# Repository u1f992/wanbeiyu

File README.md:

# Wanbeiyu

🍊 Wanbeiyu (晩白柚) is a project designed to enable control of the Nintendo 3DS series through serial communication. It succeeds the Qingpi project.

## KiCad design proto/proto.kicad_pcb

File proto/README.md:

# ATmega32U4設計メモ

## 電源回路

<figure>
<figcaption><a href="https://ww1.microchip.com/downloads/en/DeviceDoc/Atmel-7766-8-bit-AVR-ATmega16U4-32U4_Datasheet.pdf">Atmel-7766J-USB-ATmega16U4/32U4-Datasheet_04/2016</a> P.258「21.3.2 Self Powered Device」Figure 21-5. Typical Self Powered Application with 3.4V to 5.5V I/O</figcaption>

</figure>

## セラロック選定

ATmega32U4を搭載した小型のArduino互換基板に搭載されているセラロックのベース品番は、村田製作所の「CSTNE16M0V\*」のようだ（[参考](https://electronics.stackexchange.com/a/665240)）。適合するセラロックは「[SimSurfing: IC-タイミングデバイス検索ツール](https://ds.murata.co.jp/simsurfing/ic-timing-device.html)」で検索できる。ATmega32U4そのものは登録されていないので、ATmega32M1、ATmega32C1で検索した。

<details>
<summary>2025-05-09T04:07:26.697Z</summary>
<figure>
<figcaption><a href="https://ds.murata.co.jp/simsurfing/ic-timing-device.html?lcid=ja&icmaker=Microchip&icname=ATmega32M1&tdhin=CSTNE16M0V&spec_application=0&supplystatus=0&kosa=0&tempL=0&tempH=0">ATmega32M1</a></figcaption>

|IC品名|IC備考|ICメーカー|品番|適用用途[^1]|ステータス[^2]|発振周波数\[MHz]|周波数許容偏差|CL1\[pF][^3]|CL2\[pF][^4]|Rf\[ohm]|Rd\[ohm]|IC電圧(min.)\[V]|IC電圧(max.)\[V]|使用温度(min.)\[deg.C]|使用温度(max.)\[deg.C]|IC Application|
|---|---|---|---|:---:|:---:|---|---|---|---|---|---|---|---|---|---|---|
|ATmega32M1|CKSEL:111|Microchip|CSTNE16M0V53C000R0|`APS`|`生産中`|16|+/-0.5%|15|15|Open|0|4.5|5.5|-40|125||
|ATmega32M1|CKSEL:111|Microchip|CSTNE16M0VH3C000R0|`APS`|`生産中`|16|+/-0.07%|15|15|Open|0|4.5|5.5|-40|125||

</figure>

[^1]: <dl><dt><code>CE</code></dt><dd>民生機器</dd><dt><code>IE</code></dt><dd>産業機器</dd><dt><code>AIC</code></dt><dd>自動車用インフォテインメント / コンフォート機器</dd><dt><code>APS</code></dt><dd>自動車用パワートレイン / セーフティ機器</dd><dt><code>MAB</code></dt><dd>医療機器 [GHTF A/B]</dd><dt><code>MC</code></dt><dd>医療機器 [GHTF C]</dd><dt><code>MD</code></dt><dd>医療機器 [GHTF D]</dd><dt><code>MeI</code></dt><dd>インプラント除く医療機器 [GHTF A/B/C]</dd><dt><code>MI</code></dt><dd>インプラント医療機器または医療機器 [GHTF D]</dd><dt><code>MeS</code></dt><dd>インプラント・手術・自動投与用途除く医療機器 [GHTF A/B/C]</dd><dt><code>ME</code></dt><dd>モバイル機器</dd><dt><code>MC</code></dt><dd>モバイル通信</dd><dt><code>IeT</code></dt><dd>運輸・設備・商用エネルギー関連を除く産業機器</dd><dt><code>CDT</code></dt><dd>民生機器-差動伝送</dd><dt><code>HDD</code></dt><dd>HDD</dd><dt><code>DFD</code></dt><dd>重送検知</dd><dt><code>AaM</code></dt><dd>自動車用機器 <a href="https://www.murata.com/contactform?Product=Capacitor">[ムラタへ問合せ要]</a></dd><dt><code>MaM</code></dt><dd>医療機器 <a href="https://www.murata.com/contactform?Product=Capacitor">[ムラタへ問合せ要]</a></dd></dl>
[^2]: <figure><figcaption>「製品ステータス」の説明</figcaption><dl><dt><code>開発中</code></dt><dd>開発中の製品です。サンプル対応可否、量産時期についてはお問い合わせください。</dd><dt><code>生産中</code></dt><dd>量産、販売中の製品です。</dd><dt><code>NRND</code></dt><dd>新モデルへの部品採用を控えていただきたい製品です。<br>(Not Recommended for New Design)</dd><dt><code>生産中止予定</code></dt><dd>生産中止予定の製品であり、最終受注期限及び最終生産時期が表示されている場合があります。<br>最終受注期限までに、必要数量の連絡をお願いします。</dd><dt><code>生産中止</code></dt><dd>生産を中止しており、ご注文を受け付けていない製品です。</dd></dl></figure>
[^3]: 水晶振動子：外付け容量<br>セラロック：内蔵容量
[^4]: 水晶振動子：外付け容量<br>セラロック：内蔵容量

<figure>
<figcaption><a href="https://ds.murata.co.jp/simsurfing/ic-timing-device.html?lcid=ja&icmaker=Microchip&icname=ATmega32C1&tdhin=CSTNE16M0V&spec_application=0&supplystatus=0&kosa=0&tempL=0&tempH=0">ATmega32C1</a></figcaption>

|IC品名|IC備考|ICメーカー|品番|適用用途[^1]|ステータス[^2]|発振周波数\[MHz]|周波数許容偏差|CL1\[pF][^3]|CL2\[pF][^4]|Rf\[ohm]|Rd\[ohm]|IC電圧(min.)\[V]|IC電圧(max.)\[V]|使用温度(min.)\[deg.C]|使用温度(max.)\[deg.C]|IC Application|
|---|---|---|---|:---:|:---:|---|---|---|---|---|---|---|---|---|---|---|
|ATmega32C1|CKSEL:111|Microchip|CSTNE16M0V53C000R0|`APS`|`生産中`|16|+/-0.5%|15|15|Open|0|4.5|5.5|-40|125||
|ATmega32C1|CKSEL:111|Microchip|CSTNE16M0VH3C000R0|`APS`|`生産中`|16|+/-0.07%|15|15|Open|0|4.5|5.5|-40|125||

</figure>
</details>

[CSTNE16M0V53C000R0](https://www.digikey.jp/ja/products/detail/murata-electronics/CSTNE16M0V53C000R0/8747730)と[CSTNE16M0VH3C000R0](https://www.digikey.jp/ja/products/detail/murata-electronics/CSTNE16M0VH3C000R0/8747732)の違いは周波数許容偏差で、後者のほうが高精度になっている。前者のほうが安価なので、こちらを使用する。

- [CSTNE16M0V53C000R0|セラミック発振子/水晶振動子|タイミングデバイス|村田製作所](https://www.murata.com/ja-jp/products/productdetail?partno=CSTNE16M0V53C000R0)
- [CSTNE16M0V53C000R0 footprint & symbol by Murata | SnapMagic Search](https://www.snapeda.com/parts/CSTNE16M0V53C000R0/Murata/view-part/)

## その他

### DS4424（DS4424N+／DS4424N+T&R）

> T&R = Tape and reel.
> 
> [DS4422-DS4424.pdf](https://www.analog.com/media/en/technical-documentation/data-sheets/DS4422-DS4424.pdf), 19-4744; Rev 2; 9/17, p.1

- [DS4424 Datasheet and Product Info | Analog Devices](https://www.analog.com/en/products/ds4424.html)
- ★[DS4424N+ footprint, schematic symbol and 3D model by Analog Devices](https://componentsearchengine.com/part-view/DS4424N%2B/Analog%20Devices)（SamacSys）
- [DS4424N+T&R footprint, schematic symbol and 3D model by Analog Devices](https://componentsearchengine.com/part-view/DS4424N%2BT%26R/Analog%20Devices)（SamacSys）
- [Analog Devices / Maxim Integrated ds4424n+: Symbol, Footprint, 3D STEP Model | Ultra Librarian](https://app.ultralibrarian.com/details/bd464822-1067-11e9-ab3a-0a3560a4cccc/Analog-Devices-Maxim-Integrated/ds4424n-?uid=124205470)
- [Analog Devices / Maxim Integrated DS4424N+T&R: Symbol, Footprint, 3D STEP Model | Ultra Librarian](https://app.ultralibrarian.com/details/f838bba7-106d-11e9-ab3a-0a3560a4cccc/Analog-Devices-Maxim-Integrated/DS4424N-T-R?uid=124205471)
- [DS4424N+ footprint & symbol by Analog Devices | SnapMagic Search](https://www.snapeda.com/parts/DS4424N+/Analog%20Devices/view-part/)
- [DS4424N+T&R footprint & symbol by Analog Devices | SnapMagic Search](https://www.snapeda.com/parts/DS4424N%2BT%26R/Analog%20Devices/view-part/)

SamacSysには「This model has been built in collaboration with the manufacturer.」とある。品番がシンプルな方がファイルの取り回しにトラブルがないのでDS4424N+を使用。

### MCP659（MCP659-E/ML）

- [MCP659 | Microchip Technology](https://www.microchip.com/en-us/product/mcp659)
- [MCP659-E/ML footprint, schematic symbol and 3D model by Microchip](https://componentsearchengine.com/part-view/MCP659-E%2FML/Microchip)（SamacSys）
- [Microchip MCP659-E/ML: Symbol, Footprint, 3D STEP Model | Ultra Librarian](https://app.ultralibrarian.com/details/e2c9e99d-c6b2-11e9-ab3a-0a3560a4cccc/Microchip/MCP659-E-ML?uid=20012028)
- [MCP659-E/ML footprint & symbol by Microchip | SnapMagic Search](https://www.snapeda.com/parts/MCP659-E/ML/Microchip/view-part/)

### AD8403（AD8403ARU1／AD8403ARUZ1）

> Z = RoHS Compliant Part.
> 
> [AD8400_8402_8403.pdf](https://www.analog.com/media/en/technical-documentation/data-sheets/AD8400_8402_8403.pdf), Rev. E, p.31

- [AD8403 Datasheet and Product Info | Analog Devices](https://www.analog.com/en/products/ad8403.html)
- [AD8403ARUZ1-REEL footprint, schematic symbol and 3D model by Analog Devices](https://componentsearchengine.com/part-view/AD8403ARUZ1-REEL/Analog%20Devices)（SamacSys）
- [Analog Devices Inc AD8403ARUZ1: Symbol, Footprint, 3D STEP Model | Ultra Librarian](https://app.ultralibrarian.com/details/6c0e6e13-106d-11e9-ab3a-0a3560a4cccc/Analog-Devices-Inc/AD8403ARUZ1?uid=446994)
- [Analog Devices Inc AD8403ARUZ1-REEL: Symbol, Footprint, 3D STEP Model | Ultra Librarian](https://app.ultralibrarian.com/details/6c0e708d-106d-11e9-ab3a-0a3560a4cccc/Analog-Devices-Inc/AD8403ARUZ1-REEL?uid=446995)

### MAX14662（MAX14662ETI+／MAX14662ETI+T）

> T = Tape and reel
> 
> [MAX14662.pdf](https://www.analog.com/media/en/technical-documentation/data-sheets/MAX14662.pdf), 19-7308; Rev 1; 6/14, p.22

- [MAX14662 Datasheet and Product Info | Analog Devices](https://www.analog.com/en/products/max14662.html)
- [MAX14662ETI+ footprint, schematic symbol and 3D model by Analog Devices](https://componentsearchengine.com/part-view/MAX14662ETI%2B/Analog%20Devices)（SamacSys）
- [MAX14662ETI+T footprint, schematic symbol and 3D model by Analog Devices](https://componentsearchengine.com/part-view/MAX14662ETI%2BT/Analog%20Devices)（SamacSys）
- [Analog Devices / Maxim Integrated MAX14662ETI+: Symbol, Footprint, 3D STEP Model | Ultra Librarian](https://app.ultralibrarian.com/details/9a478c29-10a1-11e9-ab3a-0a3560a4cccc/Analog-Devices-Maxim-Integrated/MAX14662ETI-?uid=124207957)
- [Analog Devices / Maxim Integrated MAX14662ETI+T: Symbol, Footprint, 3D STEP Model | Ultra Librarian](https://app.ultralibrarian.com/details/98663d0d-10a3-11e9-ab3a-0a3560a4cccc/Analog-Devices-Maxim-Integrated/MAX14662ETI-T?uid=124207958)
- [MAX14662ETI+ footprint & symbol by Analog Devices | SnapMagic Search](https://www.snapeda.com/parts/MAX14662ETI%2B/Analog%20Devices/view-part/)
- [MAX14662ETI+T footprint & symbol by Analog Devices | SnapMagic Search](https://www.snapeda.com/parts/MAX14662ETI%2BT/Analog%20Devices/view-part/)
- [MAX14662ETI+ footprint & symbol by Maxim Integrated | SnapMagic Search](https://www.snapeda.com/parts/MAX14662ETI%2B/Maxim%20Integrated%20Products/view-part/)
- [MAX14662ETI+T footprint & symbol by Maxim Integrated | SnapMagic Search](https://www.snapeda.com/parts/MAX14662ETI%2BT/Maxim%20Integrated%20Products/view-part/)

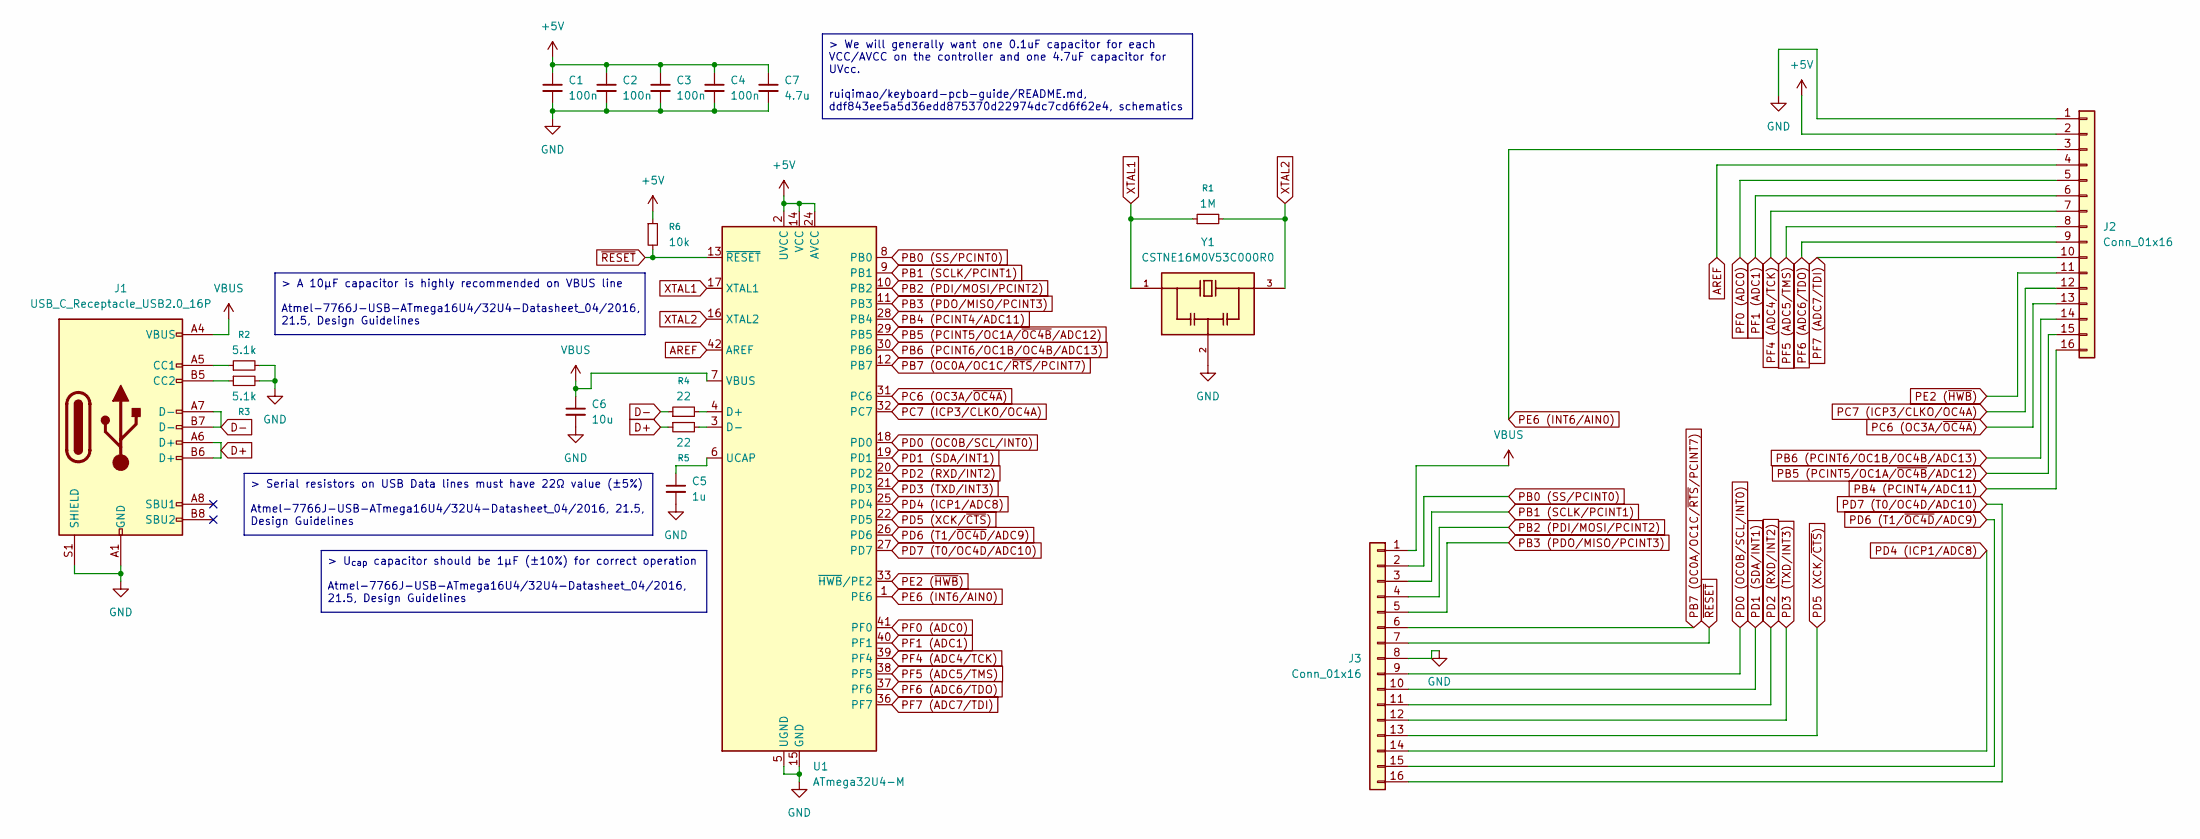
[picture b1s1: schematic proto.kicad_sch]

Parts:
C1, C2, C3, C4: 100n; C_0402_1005Metric
C5: 1u; C_0402_1005Metric
C6: 10u; C_0402_1005Metric
C7: 4.7u; C_0402_1005Metric
J1: USB_C_Receptacle_USB2.0_16P; USB_C_Receptacle_HRO_TYPE-C-31-M-12
J2, J3: Conn_01x16; PinHeader_1x16_P2.54mm_Vertical
R1: 1M; R_0402_1005Metric
R2, R3: 5.1k; R_0402_1005Metric
R4, R5: 22; R_0402_1005Metric
R6: 10k; R_0402_1005Metric
U1: ATmega32U4-M; QFN-44-1EP_7x7mm_P0.5mm_EP5.2x5.2mm
Y1: CSTNE16M0V53C000R0; OSC_CSTNE16M0V53C000R0; PARTREV JGC42-8853B

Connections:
+5V: C1.1, C2.1, C3.1, C4.1, C7.1, J2.2, R6.1, U1.2 (UVCC), U1.14 (VCC), U1.24 (AVCC), U1.34 (VCC), U1.44 (AVCC)
AREF: J2.4, U1.42 (AREF)
D+: J1.A6 (D+), J1.B6 (D+), R5.1
D-: J1.A7 (D-), J1.B7 (D-), R4.1
GND: C1.2, C2.2, C3.2, C4.2, C5.2, C6.2, C7.2, J1.A1 (GND), J1.A12 (GND), J1.B1 (GND), J1.B12 (GND), J1.S1 (SHIELD), J2.1, J3.8, R2.2, R3.2, U1.5 (UGND), U1.15 (GND), U1.23 (GND), U1.35 (GND), U1.43 (GND), U1.45 (GND), Y1.2
unnamed: J1.A5 (CC1), R2.1
unnamed: J1.B5 (CC2), R3.1
unnamed: R4.2, U1.4 (D+)
unnamed: R5.2, U1.3 (D-)
unnamed: C5.1, U1.6 (UCAP)
PB0 (SS/PCINT0): J3.2, U1.8 (PB0)
PB1 (SCLK/PCINT1): J3.3, U1.9 (PB1)
PB2 (PDI/MOSI/PCINT2): J3.4, U1.10 (PB2)
PB3 (PDO/MISO/PCINT3): J3.5, U1.11 (PB3)
PB4 (PCINT4/ADC11): J2.16, U1.28 (PB4)
PB5 (PCINT5/OC1A/~OC4B/ADC12): J2.15, U1.29 (PB5)
PB6 (PCINT6/OC1B/OC4B/ADC13): J2.14, U1.30 (PB6)
PB7 (OC0A/OC1C/~RTS/PCINT7): J3.6, U1.12 (PB7)
PC6 (OC3A/~OC4A): J2.13, U1.31 (PC6)
PC7 (ICP3/CLKO/OC4A): J2.12, U1.32 (PC7)
PD0 (OC0B/SCL/INT0): J3.9, U1.18 (PD0)
PD1 (SDA/INT1): J3.10, U1.19 (PD1)
PD2 (RXD/INT2): J3.11, U1.20 (PD2)
PD3 (TXD/INT3): J3.12, U1.21 (PD3)
PD4 (ICP1/ADC8): J3.14, U1.25 (PD4)
PD5 (XCK/~CTS): J3.13, U1.22 (PD5)
PD6 (T1/~OC4D/ADC9): J3.15, U1.26 (PD6)
PD7 (T0/OC4D/ADC10): J3.16, U1.27 (PD7)
PE2 (~HWB): J2.11, U1.33 (~HWB/PE2)
PE6 (INT6/AIN0): J2.3, U1.1 (PE6)
PF0 (ADC0): J2.5, U1.41 (PF0)
PF1 (ADC1): J2.6, U1.40 (PF1)
PF4 (ADC4/TCK): J2.7, U1.39 (PF4)
PF5 (ADC5/TMS): J2.8, U1.38 (PF5)
PF6 (ADC6/TDO): J2.9, U1.37 (PF6)
PF7 (ADC7/TDI): J2.10, U1.36 (PF7)
VBUS: C6.1, J1.A4 (VBUS), J1.A9 (VBUS), J1.B4 (VBUS), J1.B9 (VBUS), J3.1, U1.7 (VBUS)
XTAL1: R1.1, U1.17 (XTAL1), Y1.1
XTAL2: R1.2, U1.16 (XTAL2), Y1.3
~RESET: J3.7, R6.2, U1.13 (~RESET)

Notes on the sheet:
> A 10µF capacitor is highly recommended on VBUS line Atmel-7766J-USB-ATmega16U4/32U4-Datasheet_04/2016, 21.5, Design Guidelines
> U_{cap} capacitor should be 1µF (±10%) for correct operation Atmel-7766J-USB-ATmega16U4/32U4-Datasheet_04/2016, 21.5, Design Guidelines
> Serial resistors on USB Data lines must have 22Ω value (±5%) Atmel-7766J-USB-ATmega16U4/32U4-Datasheet_04/2016, 21.5, Design Guidelines
> We will generally want one 0.1uF capacitor for each VCC/AVCC on the controller and one 4.7uF capacitor for UVcc. ruiqimao/keyboard-pcb-guide/README.md, ddf843ee5a5d36edd875370d22974dc7cd6f62e4, schematics

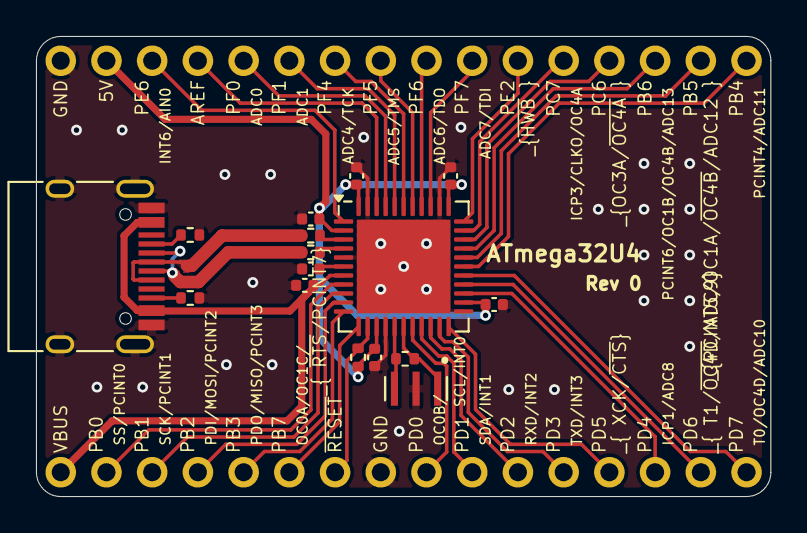
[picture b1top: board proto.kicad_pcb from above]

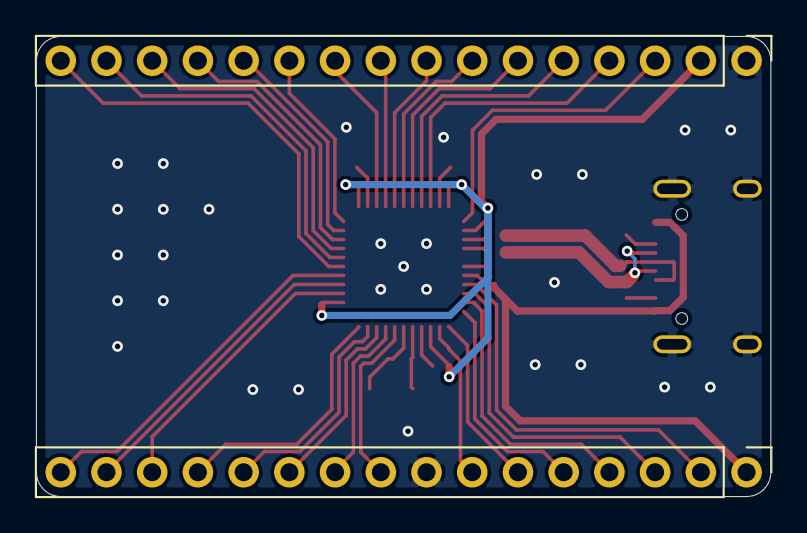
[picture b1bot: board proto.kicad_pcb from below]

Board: 2 copper layers, 40.8 x 25.6 mm, 18 parts (2 on the bottom side), 40 nets.

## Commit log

2025-01-16 Add files
2025-01-16 Create LICENSE
2025-03-16 Update core
2025-03-23 temp
2025-03-26 Use new HAL
2025-03-26 Unify button states into a 16-bit bitfield
2025-03-26 Add test
2025-03-26 Read input from HAL
2025-03-27 Add helper.h
2025-03-27 Inverts pin assignments
2025-03-27 Refactor console_set to use function pointer array
2025-03-27 Replace wanbeiyu_t with static singleton instance
2025-03-27 Extract parser logic into separate module
2025-03-27 Modularize components
2025-03-27 Add license notice
2025-03-27 Add tests (buttons, touch_screen)
2025-03-28 Add documents
2025-03-29 Fix C Stick
2025-03-30 Add hook
2025-03-30 firmware
2025-03-30 Format
2025-03-30 Extend hooks
2025-03-30 Blink
2025-04-19 Fix SPI comm
2025-04-19 Add python script
2025-04-19 TopDesign
2025-04-24 Fix SPI blocking writes
2025-04-24 Update test script
2025-04-25 Lights off for 32ms
2025-04-27 Change switch
2025-04-27 WIP: CirclePad
2025-04-28 Start Opamps
2025-04-28 Use switch for CirclePads
2025-04-29 Add CStick
2025-04-29 Start CStick
2025-04-29 Use switch for CSticks
2025-05-06 Change bandwidth
2025-05-10 Add prototyping board
2025-05-11 Add prototyping board (Rev 0)
